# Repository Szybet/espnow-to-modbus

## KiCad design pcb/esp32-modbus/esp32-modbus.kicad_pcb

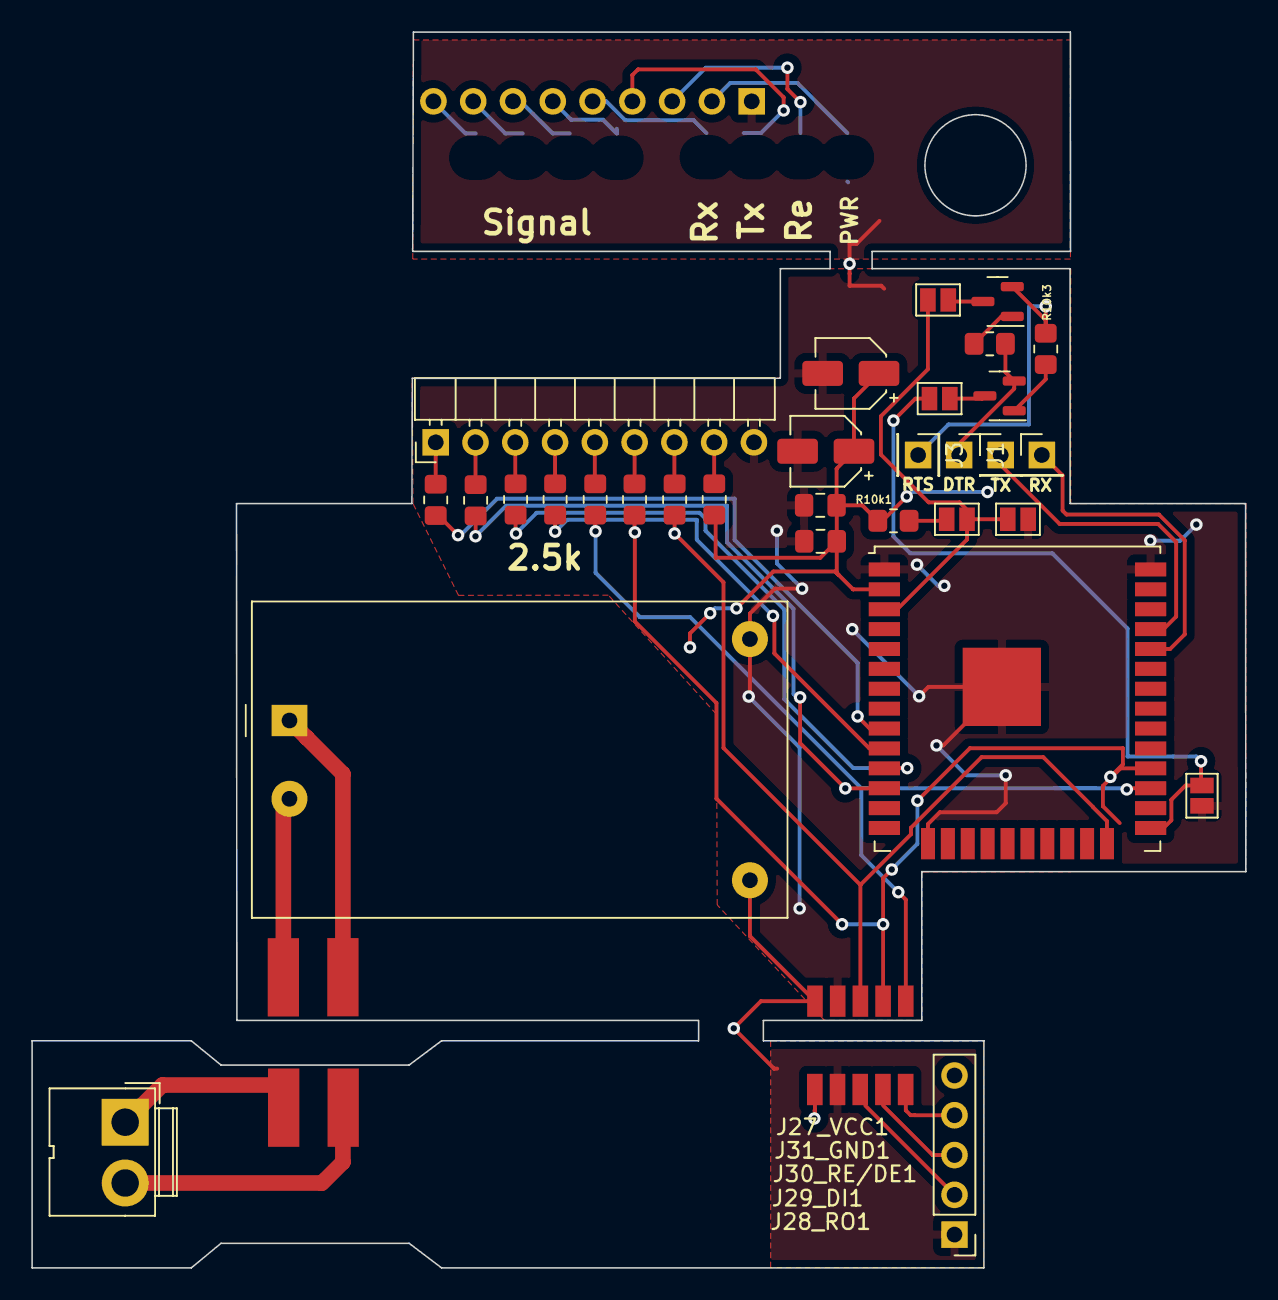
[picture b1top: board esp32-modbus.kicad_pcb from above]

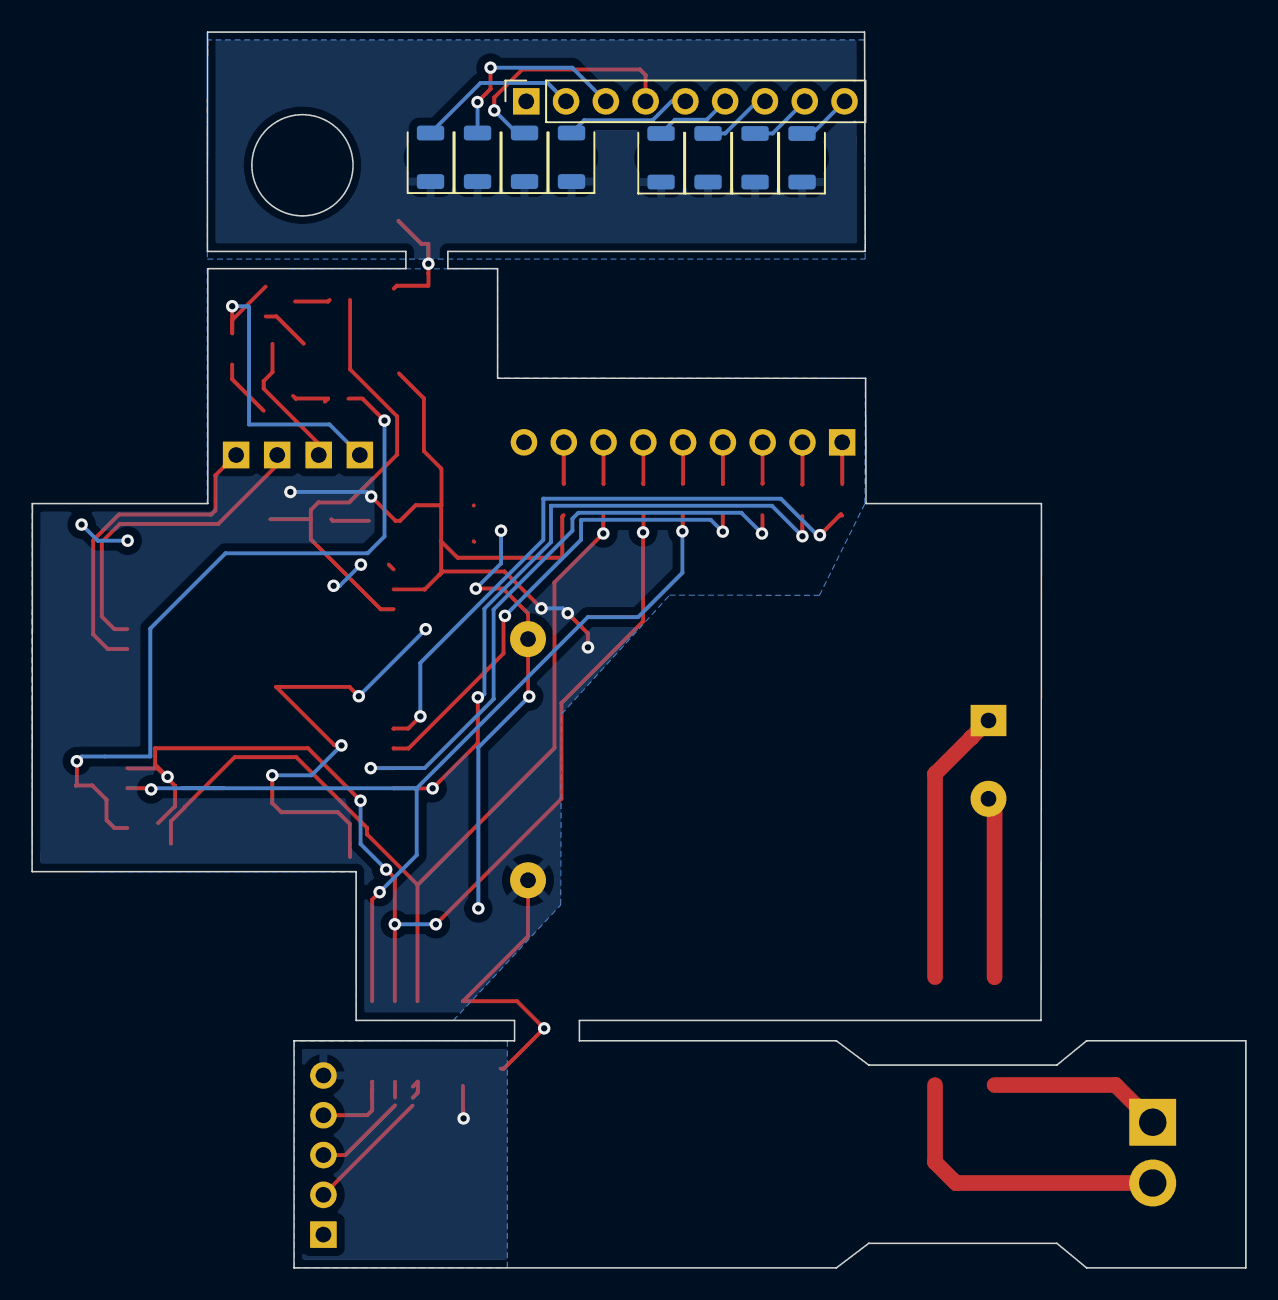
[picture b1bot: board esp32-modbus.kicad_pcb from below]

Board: 2 copper layers, 77.5 x 78.9 mm, 54 parts (9 on the bottom side), 46 nets.

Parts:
C1, C2: C; C_0805_2012Metric_Pad1.18x1.45mm_HandSolder
C3, C4: C_Polarized; CP_Elec_4x5.8
D1, D2, D3, D4, D5, D6, D7, D8: LED; LED_1206_3216Metric_ReverseMount_Hole1.8x2.4mm
J1, J3, J4, J5: Conn_01x01_Male; PinHeader_1x01_P2.54mm_Vertical
J2: Conn_01x05_Male; PinHeader_1x05_P2.54mm_Vertical
J6: Screw_Terminal_01x02; JWT_A3963_1x02_P3.96mm_Vertical
J7: Conn_01x09_Male; PinSocket_1x09_P2.54mm_Vertical
J8: Conn_01x09_Male; PinHeader_1x09_P2.54mm_Horizontal
J9, J10, J12, J13: Conn_01x01_Male; TestPoint_Pad_4.0x4.0mm
J22, J23, J24, J25, J26, J27_VCC1, J28_RO1, J29_DI1, J30_RE/DE1, J31_GND1: Conn_01x01_Male; TestPoint_Pad_4.0x4.0mm2
JP1, JP2, JP3, JP4, JP5: SolderJumper_2_Open; SolderJumper-2_P1.3mm_Open_Pad1.0x1.5mm
PS1: HLK-PM03; Converter_ACDC_HiLink_HLK-PMxx
Q1, Q2: BC817; SOT-23
R2.5k, R2.5k1, R2.5k2, R2.5k4, R2.5k5, R2.5k6, R2.5k7, R2.5k8, R10k1, R10k2, R10k3: R; R_0805_2012Metric_Pad1.20x1.40mm_HandSolder
U1: ESP32-WROOM-32U

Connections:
+3.3V: C1.1, C2.1, C3.1, C4.1, J26.1, PS1.4 (+Vout), R2.5k1.1, R10k1.1, U1.2 (VDD)
+3.3VA: J2.5, J27_VCC1.1
/EN: JP1.1 (A), JP3.2 (B), JP4.2 (B), U1.3 (EN)
/GPIO0: JP2.1 (A), JP5.2 (B), U1.25 (IO0)
/GPIO2: J24.1, R2.5k2.1, U1.24 (IO2)
/GPIO25: R2.5k5.1, U1.10 (IO25)
/GPIO26: R2.5k6.1, U1.11 (IO26)
/GPIO27: R2.5k7.1, U1.12 (IO27)
/GPIO33: R2.5k8.1, U1.9 (IO33)
/RX: J22.1, R2.5k4.1, U1.27 (IO16)
/RXP: J4.1, U1.34 (RXD0/IO3)
/TX: J23.1, R2.5k.1, U1.28 (IO17)
/TXD: J5.1, U1.35 (TXD0/IO1)
GND: C1.2, C2.2, C3.2, C4.2, J8.9, J25.1, JP1.2 (B), JP2.2 (B), PS1.3 (-Vout), U1.1 (GND), U1.15 (GND), U1.38 (GND), U1.39 (GND)
GND1: J2.1, J31_GND1.1
GND2: D1.1 (K), D2.1 (K), D3.1 (K), D4.1 (K), D5.1 (K), D6.1 (K), D7.1 (K), D8.1 (K), J7.1
unnamed: D1.2 (A), J7.3
unnamed: D2.2 (A), J7.4
unnamed: D3.2 (A), J7.5
unnamed: D4.2 (A), J7.2
unnamed: D5.2 (A), J7.6
unnamed: D6.2 (A), J7.7
unnamed: D7.2 (A), J7.8
unnamed: D8.2 (A), J7.9
unnamed: J1.1, Q2.2 (E), R10k2.1
unnamed: J2.2, J30_RE/DE1.1
unnamed: J2.3, J29_DI1.1
unnamed: J2.4, J28_RO1.1
unnamed: J3.1, Q1.2 (E), R10k3.1
unnamed: J6.2, J9.1
unnamed: J8.1, R2.5k8.2
unnamed: J8.2, R2.5k7.2
unnamed: J8.3, R2.5k6.2
unnamed: J8.4, R2.5k5.2
unnamed: J8.5, R2.5k4.2
unnamed: J8.6, R2.5k.2
unnamed: J8.7, R2.5k2.2
unnamed: J8.8, R2.5k1.2
unnamed: J6.1, J10.1
unnamed: J12.1, PS1.1 (AC/L)
unnamed: J13.1, PS1.2 (AC/N)
unnamed: JP3.1 (A), R10k1.2
unnamed: JP4.1 (A), Q1.3 (C)
unnamed: JP5.1 (A), Q2.3 (C)
unnamed: Q1.1 (B), R10k2.2
unnamed: Q2.1 (B), R10k3.2

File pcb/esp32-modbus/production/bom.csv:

Designator,Footprint,Quantity,Value,LCSC Part #
J3,PinHeader_1x01_P2.54mm_Vertical,1,Conn_01x01_Male,
J24,TestPoint_Pad_4.0x4.0mm2,1,Conn_01x01_Male,
JP2,SolderJumper-2_P1.3mm_Open_Pad1.0x1.5mm,1,SolderJumper_2_Open,
J1,PinHeader_1x01_P2.54mm_Vertical,1,Conn_01x01_Male,
R2.5k8,R_0805_2012Metric_Pad1.20x1.40mm_HandSolder,1,R,
JP3,SolderJumper-2_P1.3mm_Open_Pad1.0x1.5mm,1,SolderJumper_2_Open,
R10k3,R_0805_2012Metric_Pad1.20x1.40mm_HandSolder,1,R,
R10k2,R_0805_2012Metric_Pad1.20x1.40mm_HandSolder,1,R,
J29_DI1,TestPoint_Pad_4.0x4.0mm2,1,Conn_01x01_Male,
R2.5k2,R_0805_2012Metric_Pad1.20x1.40mm_HandSolder,1,R,
J5,PinHeader_1x01_P2.54mm_Vertical,1,Conn_01x01_Male,
U1,ESP32-WROOM-32U,1,ESP32-WROOM-32U,
J8,PinHeader_1x09_P2.54mm_Horizontal,1,Conn_01x09_Male,
J2,PinHeader_1x05_P2.54mm_Vertical,1,Conn_01x05_Male,
R2.5k7,R_0805_2012Metric_Pad1.20x1.40mm_HandSolder,1,R,
R2.5k,R_0805_2012Metric_Pad1.20x1.40mm_HandSolder,1,R,
JP5,SolderJumper-2_P1.3mm_Open_Pad1.0x1.5mm,1,SolderJumper_2_Open,
Q2,SOT-23,1,BC817,
C3,CP_Elec_4x5.8,1,C_Polarized,
R2.5k4,R_0805_2012Metric_Pad1.20x1.40mm_HandSolder,1,R,
J25,TestPoint_Pad_4.0x4.0mm2,1,Conn_01x01_Male,
J27_VCC1,TestPoint_Pad_4.0x4.0mm2,1,Conn_01x01_Male,
C4,CP_Elec_4x5.8,1,C_Polarized,
R2.5k6,R_0805_2012Metric_Pad1.20x1.40mm_HandSolder,1,R,
R2.5k5,R_0805_2012Metric_Pad1.20x1.40mm_HandSolder,1,R,
J13,TestPoint_Pad_4.0x4.0mm,1,Conn_01x01_Male,
J9,TestPoint_Pad_4.0x4.0mm,1,Conn_01x01_Male,
J10,TestPoint_Pad_4.0x4.0mm,1,Conn_01x01_Male,
R2.5k1,R_0805_2012Metric_Pad1.20x1.40mm_HandSolder,1,R,
J23,TestPoint_Pad_4.0x4.0mm2,1,Conn_01x01_Male,
J22,TestPoint_Pad_4.0x4.0mm2,1,Conn_01x01_Male,
J12,TestPoint_Pad_4.0x4.0mm,1,Conn_01x01_Male,
J28_RO1,TestPoint_Pad_4.0x4.0mm2,1,Conn_01x01_Male,
J6,JWT_A3963_1x02_P3.96mm_Vertical,1,Screw_Terminal_01x02,
Q1,SOT-23,1,BC817,
JP4,SolderJumper-2_P1.3mm_Open_Pad1.0x1.5mm,1,SolderJumper_2_Open,
J26,TestPoint_Pad_4.0x4.0mm2,1,Conn_01x01_Male,
JP1,SolderJumper-2_P1.3mm_Open_Pad1.0x1.5mm,1,SolderJumper_2_Open,
C1,C_0805_2012Metric_Pad1.18x1.45mm_HandSolder,1,C,
J30_RE/DE1,TestPoint_Pad_4.0x4.0mm2,1,Conn_01x01_Male,
PS1,Converter_ACDC_HiLink_HLK-PMxx,1,HLK-PM03,
J4,PinHeader_1x01_P2.54mm_Vertical,1,Conn_01x01_Male,
C2,C_0805_2012Metric_Pad1.18x1.45mm_HandSolder,1,C,
R10k1,R_0805_2012Metric_Pad1.20x1.40mm_HandSolder,1,R,
J31_GND1,TestPoint_Pad_4.0x4.0mm2,1,Conn_01x01_Male,
D1,LED_1206_3216Metric_ReverseMount_Hole1.8x2.4mm,1,LED,
D7,LED_1206_3216Metric_ReverseMount_Hole1.8x2.4mm,1,LED,
D4,LED_1206_3216Metric_ReverseMount_Hole1.8x2.4mm,1,LED,
D8,LED_1206_3216Metric_ReverseMount_Hole1.8x2.4mm,1,LED,
D6,LED_1206_3216Metric_ReverseMount_Hole1.8x2.4mm,1,LED,
D3,LED_1206_3216Metric_ReverseMount_Hole1.8x2.4mm,1,LED,
D5,LED_1206_3216Metric_ReverseMount_Hole1.8x2.4mm,1,LED,
J7,PinSocket_1x09_P2.54mm_Vertical,1,Conn_01x09_Male,
D2,LED_1206_3216Metric_ReverseMount_Hole1.8x2.4mm,1,LED,

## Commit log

2022-06-11 init
2022-06-12 some tests
2022-06-14 cleaning
2022-06-14 real init
2022-06-16 fix compiling, begin with debug
2022-06-16 fix queue error, dumb C
2022-06-16 debug sending broadcast
2022-06-18 something is really wrong with lenght
2022-06-29 cleaning of espnow example code and uart
2022-06-30 gpio + uart
2022-07-03 timeouts
2022-07-05 succesfull everything, added esp01, cleaning
2022-07-06 tcp server, better uart
2022-07-06 make esp-01 comunication 100% stateless
2022-07-06 rewrite espnow sender to be 100% statefull
2022-07-06 fixes
2022-07-06 rewrite modbus to be 100% stateless
2022-07-08 watchdog not working
2022-07-08 logging, connection check in esp01
2022-07-08 sdkconfig changes - Watchdog works
2022-07-13 pcb prototype
2022-07-14 full prototype
2022-07-15 espnow rssi test code
2022-07-15 pcb update, esp01 wifi
2022-09-12 signal strength diodes
2022-09-20 numbers
